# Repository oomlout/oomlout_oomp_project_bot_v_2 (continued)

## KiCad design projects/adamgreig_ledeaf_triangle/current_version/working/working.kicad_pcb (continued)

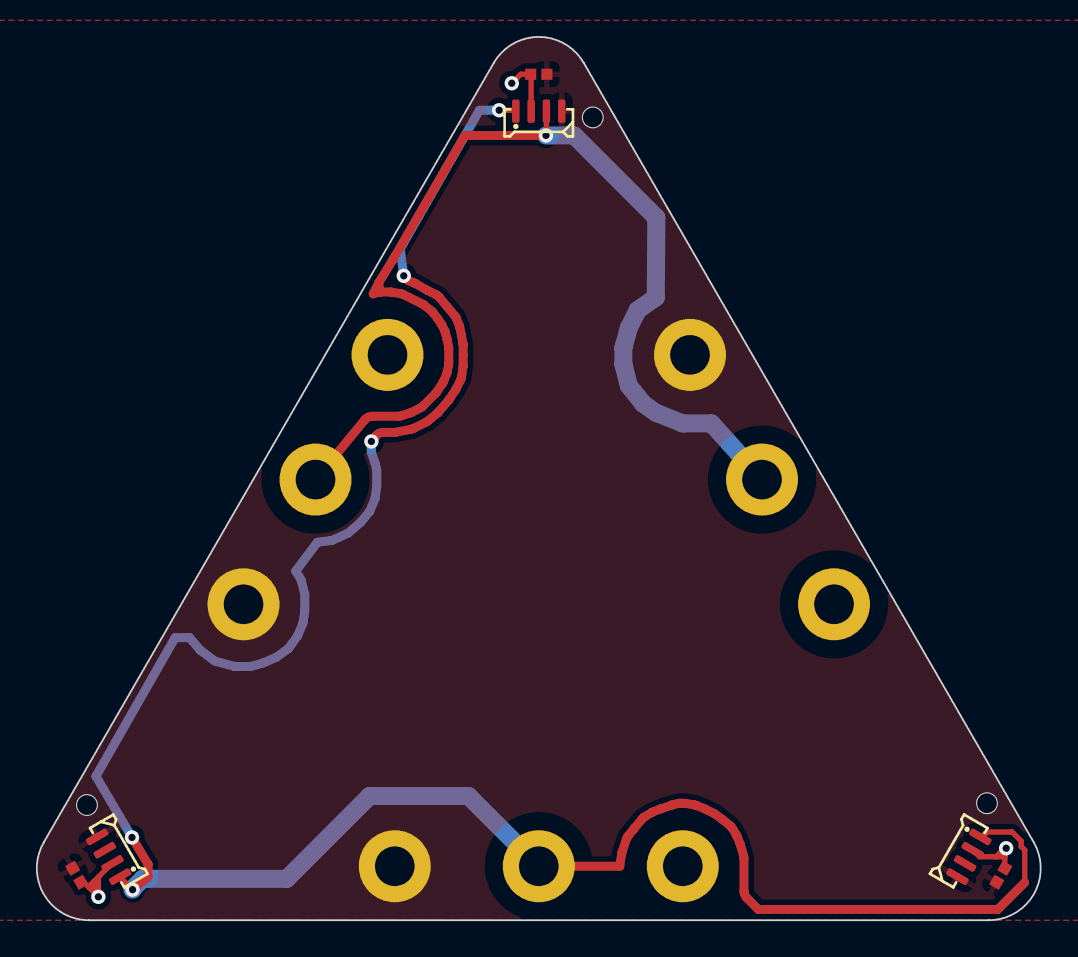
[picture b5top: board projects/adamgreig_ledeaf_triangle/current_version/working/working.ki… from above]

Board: 2 copper layers, 55.8 x 49.1 mm, 18 parts (0 on the bottom side), 4 nets.

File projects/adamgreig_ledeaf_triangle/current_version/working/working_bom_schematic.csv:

"Source:","C:\gh\oomlout_oomp_project_bot_v_2\projects\adamgreig_ledeaf_triangle\current_version\working\working.kicad_sch"
"Date:","17/09/2023 22:56:52"
"Tool:","Eeschema 7.0.6"
"Generator:","C:/Program Files/KiCad/7.0/bin/scripting/plugins/bom_csv_grouped_by_value_with_fp.py"
"Component Count:","18"
"Ref","Qnty","Value","Cmp name","Footprint","Description","Vendor","DNP"
"C1, C2, C3","3","100n","C","agg:0402","","",""
"J1, J4, J7","3","GND","CONN_01x01","agg:M2_PTH","","",""
"J2","1","DIN","CONN_01x01","agg:M2_PTH","","",""
"J3, J6, J9","3","5V","CONN_01x01","agg:M2_PTH","","",""
"J5, J8","2","DOUT","CONN_01x01","agg:M2_PTH","","",""
"LED1, LED2, LED3","3","WS2812B-4020","WS2812B-4020","agg:WS2812B-4020","Side-view RGB LED","",""
"X1, X2, X3","3","TOOLING","PART","agg:M2.5_HOLE","Generic placeholder part","",""

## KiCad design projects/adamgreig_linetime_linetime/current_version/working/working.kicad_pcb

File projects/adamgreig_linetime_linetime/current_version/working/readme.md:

# linetime
 
## summary 
* id: adamgreig_linetime_linetime
* user: adamgreig
* name: linetime
* board: linetime
* repo: https://github.com/adamgreig/linetime
* src_file_repo_kicad_pcb: hardware/linetime.kicad_pcb
* src_file_repo_kicad_pcb_link: https://github.com/adamgreig/linetime/tree/master/hardware/linetime.kicad_pcb

* src_file_repo_sch: hardware/linetime.sch
* src_file_repo_sch_link: https://github.com/adamgreig/linetime/tree/master/hardware/linetime.sch
* full details link: https://github.com/oomlout/oomlout_oomp_project_bot_v_2/tree/main/projects/adamgreig_linetime_linetime/current_version/working  

## schematic  
  
[schematic (pdf)](working_schematic.pdf) 

## pcb  

[board (pdf)](working.pdf)  

## working_bom
| Id | Designator | Footprint | Quantity | Designation | Supplier and ref |  | None | 
| --- | --- | --- | --- | --- | --- | --- | --- | 
| 1 | Y401 | XTAL-50x32 | 1 | XTAL |  |  | [''] | 
| 2 | IC201 | VTX-214-003-1xx | 1 | VTX-214-003-105 |  |  | [''] | 
| 3 | Y301 | TG-5006CG | 1 | 26M TCXO |  |  | [''] | 
| 4 | IC603 | SSOP-20 | 1 | AR1021 |  |  | [''] | 
| 5 | IC103 | SOT-23-6 | 1 | 25AA02E48 |  |  | [''] | 
| 6 | IC302 | SOT-23-5 | 1 | NC7SZ04 |  |  | [''] | 
| 7 | Q601 | SOT-23 | 1 | NFET |  |  | [''] | 
| 8 | R201 | SOT-23 | 1 | 1k/5k |  |  | [''] | 
| 9 | R202 | SOT-23 | 1 | 1k/1k |  |  | [''] | 
| 10 | D603,D604,D602,D601 | SOD-123 | 4 | ~ |  |  | [''] | 
| 11 | P301 | SMA-PTH | 1 | COAX |  |  | [''] | 
| 12 | IC203 | SC-70-6 | 1 | ADCMP601 |  |  | [''] | 
| 13 | IC401 | RJHSE-538X | 1 | RJHSE-5381 |  |  | [''] | 
| 14 | IC402 | QFN-24-EP-MICREL | 1 | KSZ8081RNx |  |  | [''] | 
| 15 | IC501 | QFN-16-EP-TI | 1 | BQ24232HA |  |  | [''] | 
| 16 | IC602 | MSOP-8 | 1 | SSM2305 |  |  | [''] | 
| 17 | IC301,IC202,IC102 | MSOP-8 | 3 | ADP3335 |  |  | [''] | 
| 18 | IC204 | MSOP-8 | 1 | ADA4528-2 |  |  | [''] | 
| 19 | IC304 | MSOP-10 | 1 | CS2100-CP |  |  | [''] | 
| 20 | IC303 | MAX-M8Q | 1 | MAX-M8Q |  |  | [''] | 
| 21 | IC101 | LQFP-144 | 1 | STM32F7xxZxTx |  |  | [''] | 
| 22 | P101 | FTSH-105-01-F-D-K | 1 | SWD |  |  | [''] | 
| 23 | J201 | DD21.01xx.1111 | 1 | FUSED INLET |  |  | [''] | 
| 24 | C203 | B32921 | 1 | X2 |  |  | [''] | 
| 25 | C201,C202 | B32921 | 2 | Y2 |  |  | [''] | 
| 26 | T201 | AVB0.35_2_X | 1 | AVB0.35/2/6 |  |  | [''] | 
| 27 | T401 | 749010012A | 1 | 749013011A |  |  | [''] | 
| 28 | D103,D102,D101 | 0603-LED | 3 | LED |  |  | [''] | 
| 29 | C209,C205,C121,C301,C308,C610,C611,C212 | 0603 | 8 | 10n |  |  | [''] | 
| 30 | C118,C117,C408 | 0603 | 3 | 2Âµ2 |  |  | [''] | 
| 31 | C208,C403,C119,C210,C211,C303,C305,C306,C307,C603,C602,C607,C411,C609,C109,C116,C115,C114,C113,C101,C112,C110,C405,C108,C107,C106,C404,C407,C102,C111,C105 | 0603 | 31 | 100n |  |  | [''] | 
| 32 | C207,C304 | 0603 | 2 | 1n |  |  | [''] | 
| 33 | C206,C204,C122,C120,C302,C104,C309 | 0603 | 7 | 1Âµ |  |  | [''] | 
| 34 | C409,C410 | 0603 | 2 | 30p |  |  | [''] | 
| 35 | C402,C406 | 0603 | 2 | 22Âµ |  |  | [''] | 
| 36 | R108,R104,R106,R107,R105 | 0603 | 5 | 47k |  |  | [''] | 
| 37 | C502,C503,C501,C103 | 0603 | 4 | 4Âµ7 |  |  | [''] | 
| 38 | C606,C604 | 0603 | 2 | 47n |  |  | [''] | 
| 39 | C605,C601,C608 | 0603 | 3 | 10Âµ |  |  | [''] | 
| 40 | R601,R602,R409,R103,R101,R102,R401 | 0603 | 7 | 1k |  |  | [''] | 
| 41 | R604,R603 | 0603 | 2 | 110k |  |  | [''] | 
| 42 | R407,R408,R405,R404,R205,R303,R411,R413,R412 | 0603 | 9 | 33 |  |  | [''] | 
| 43 | R505,R504 | 0603 | 2 | 100k |  |  | [''] | 
| 44 | R503,R410,R606,R2,R1 | 0603 | 5 | 10k |  |  | [''] | 
| 45 | R502,R204,R203 | 0603 | 3 | DNS |  |  | [''] | 
| 46 | R501 | 0603 | 1 | 4k32 |  |  | [''] | 
| 47 | L201,L401 | 0603 | 2 | FB |  |  | [''] | 
| 48 | L301 | 0603 | 1 | 27n |  |  | [''] | 
| 49 | R406 | 0603 | 1 | 6k49 |  |  | [''] | 
| 50 | R403,R402 | 0603 | 2 | 75 |  |  | [''] | 
| 51 | R302 | 0603 | 1 | 10 |  |  | [''] | 
| 52 | R605 | 0603 | 1 | 20k |  |  | [''] | 
| 53 | R301 | 0603 | 1 | 1M |  |  | [''] | 
| 54 | D301,D605,D606,D607,D608 | 0402 | 5 | ESD_DIODE |  |  | [''] | 
| 55 | C401 | 1206 | 1 | 1n 2kV |  |  | [''] | 
| 56 | LS601 | KSSG1708 | 1 | KSSG1708 |  |  | [''] | 
| 57 | R206 | 0603 | 1 | 100 |  |  | [''] | 
| 58 | U101 | MICROSD_MOLEX_503398-1892 | 1 | MICROSD |  |  | [''] | 
| 59 | IC601 | ER-CON50HT-1 | 1 | ER-TFT023-1 |  |  | [''] | 
| 60 | J501 | S02B-PASK-2 | 1 | BATT |  |  | [''] | 

## bom_schematic
| Ref | Qnty | Value | Cmp name | Footprint | Description | Vendor | DNP | 
| --- | --- | --- | --- | --- | --- | --- | --- | 
| C101, C102, C105, C106, C107, C108, C109, C110, C111, C112, C113, C114, C115, C116, C119 | 15 | 100n | C | agg:0603 |  |  |  | 
| C103 | 1 | 4Âµ7 | C | agg:0603 |  |  |  | 
| C104, C120, C122 | 3 | 1Âµ | C | agg:0603 |  |  |  | 
| C117, C118 | 2 | 2Âµ2 | C | agg:0603 |  |  |  | 
| C121 | 1 | 10n | C | agg:0603 |  |  |  | 
| D101, D102, D103 | 3 | LED | LED | agg:0603-LED |  |  |  | 
| IC101 | 1 | STM32F7xxZxTx | STM32F7xxZxTx | agg:LQFP-144 |  |  |  | 
| IC102 | 1 | ADP3335 | ADP3335 | agg:MSOP-8 |  |  |  | 
| IC103 | 1 | 25AA02E48 | 25AA02E48 | agg:SOT-23-6 |  |  |  | 
| P101 | 1 | SWD | SWD | agg:FTSH-105-01-F-D-K |  |  |  | 
| R101, R102, R103 | 3 | 1k | R | agg:0603 |  |  |  | 
| R104, R105, R106, R107, R108 | 5 | 47k | R | agg:0603 |  |  |  | 
| U101 | 1 | MICROSD | MICROSD | agg:MICROSD_MOLEX_503398-1892 |  |  |  |

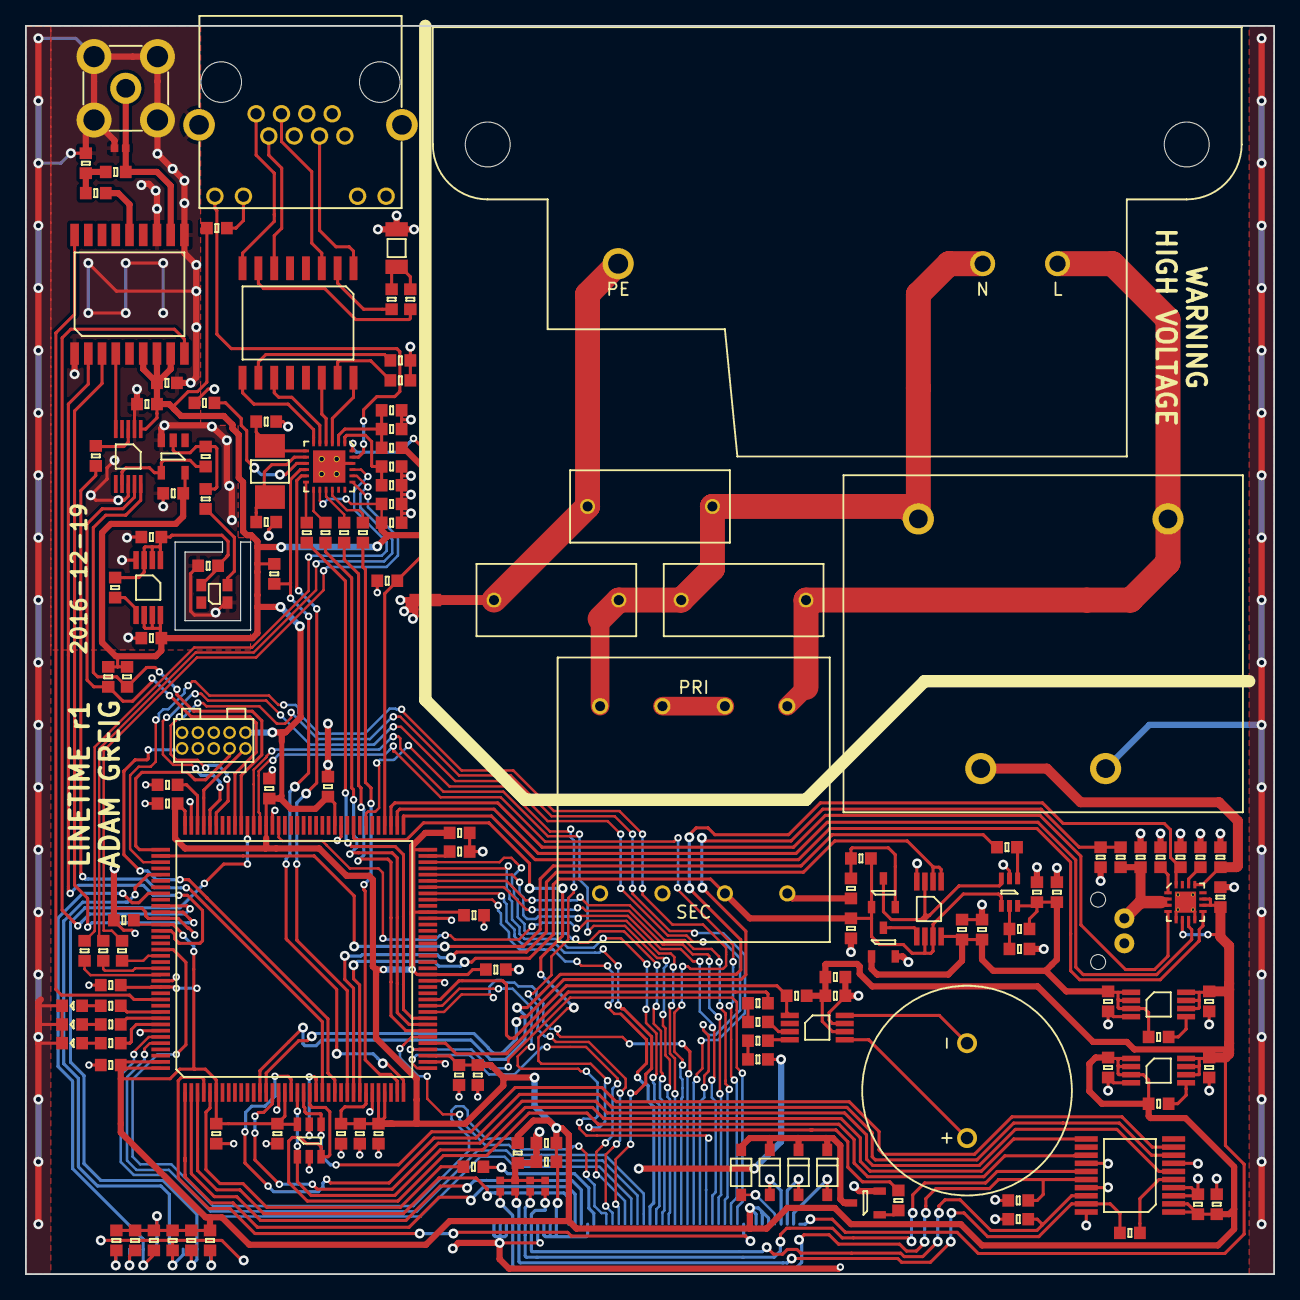
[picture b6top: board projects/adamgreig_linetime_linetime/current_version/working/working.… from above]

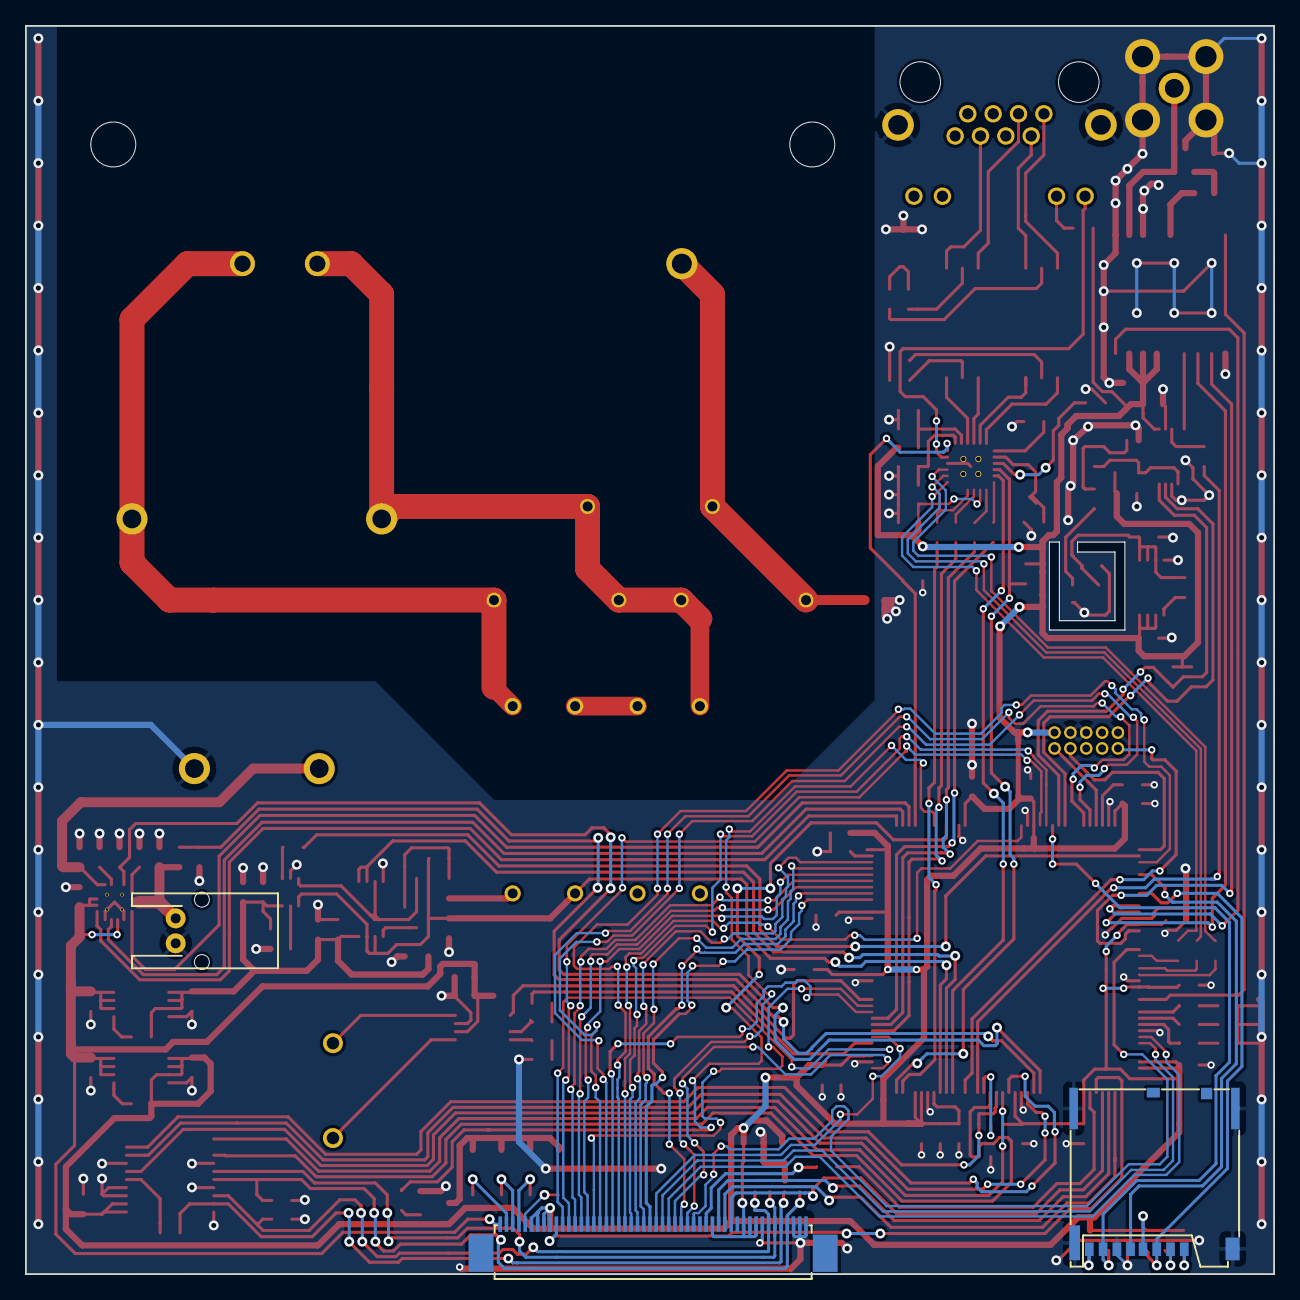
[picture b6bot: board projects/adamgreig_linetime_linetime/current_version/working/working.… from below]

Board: 2 copper layers, 100.0 x 100.0 mm, 154 parts (3 on the bottom side), 153 nets.

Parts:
C101, C102, C105, C106, C107, C108, C109, C110, C111, C112, C113, C114, C115, C116, C119, C208, C210, C211, C303, C305, C306, C307, C403, C404, C405, C407, C411, C602, C603, C607, C609: 100n; 0603
C103, C501, C502, C503: 4µ7; 0603
C104, C120, C122, C204, C206, C302, C309: 1µ; 0603
C117, C118, C408: 2µ2; 0603
C121, C205, C209, C212, C301, C308, C610, C611: 10n; 0603
C201, C202: Y2; B32921
C203: X2; B32921
C207, C304: 1n; 0603
C401: 1n 2kV; 1206
C402, C406: 22µ; 0603
C409, C410: 30p; 0603
C601, C605, C608: 10µ; 0603
C604, C606: 47n; 0603
D101, D102, D103: LED; 0603-LED
D301, D605, D606, D607, D608: ESD_DIODE; 0402
D601, D602, D603, D604: SOD-123
IC101: STM32F7xxZxTx; LQFP-144
IC102, IC202, IC301: ADP3335; MSOP-8
IC103: 25AA02E48; SOT-23-6
IC201: VTX-214-003-105; VTX-214-003-1xx
IC203: ADCMP601; SC-70-6
IC204: ADA4528-2; MSOP-8
IC302: NC7SZ04; SOT-23-5
IC303: MAX-M8Q
IC304: CS2100-CP; MSOP-10
IC401: RJHSE-5381; RJHSE-538X
IC402: KSZ8081RNx; QFN-24-EP-MICREL
IC501: BQ24232HA; QFN-16-EP-TI
IC601: ER-TFT023-1; ER-CON50HT-1
IC602: SSM2305; MSOP-8
IC603: AR1021; SSOP-20
J201: FUSED INLET; DD21.01xx.1111
J501: BATT; S02B-PASK-2
L201, L401: FB; 0603
L301: 27n; 0603
LS601: KSSG1708
P101: SWD; FTSH-105-01-F-D-K
P301: COAX; SMA-PTH
Q601: NFET; SOT-23
R1, R2, R410, R503, R606: 10k; 0603
R101, R102, R103, R401, R409, R601, R602: 1k; 0603
R104, R105, R106, R107, R108: 47k; 0603
R201: 1k/5k; SOT-23
R202: 1k/1k; SOT-23
R203, R204, R502: DNS; 0603
R205, R303, R404, R405, R407, R408, R411, R412, R413: 33; 0603
R206: 100; 0603
R301: 1M; 0603
R302: 10; 0603
R402, R403: 75; 0603
R406: 6k49; 0603
R501: 4k32; 0603
R504, R505: 100k; 0603
R603, R604: 110k; 0603
R605: 20k; 0603
T201: AVB0.35/2/6; AVB0.35_2_X
T401: 749013011A; 749010012A
U101: MICROSD; MICROSD_MOLEX_503398-1892
Y301: 26M TCXO; TG-5006CG
Y401: XTAL; XTAL-50x32

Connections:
3v3: C101.1, C102.1, C103.1, C104.1, C105.1, C106.1, C107.1, C108.1, C109.1, C110.1, C111.1, C112.1, C113.1, C114.1, C115.1, C116.1, C119.1, C121.2, C122.1, C305.1, C306.1, C307.1, C309.1, C406.2, C407.2, C601.1, C602.1, C603.1, C608.1, C609.1, IC101.6, IC101.17, IC101.30, IC101.32, IC101.33, IC101.39, IC101.52, IC101.62, IC101.72, IC101.84, IC101.95, IC101.108, IC101.121, IC101.131, IC101.143, IC101.144, IC102.1, IC102.2, IC102.3, IC103.6, IC301.6, IC301.7, IC301.8, IC302.5, IC303.6, IC303.7, IC303.8, IC304.1, IC402.14, IC601.6, IC601.7, IC601.8, IC601.9, IC601.35, IC601.40, IC601.41, IC601.42, IC603.1, IC603.2, L401.2, P101.1, R1.1, R2.1, R104.1, R105.1, R106.1, R107.1, R108.1, R401.2, R409.2, U101.4
/B2: IC101.125, IC601.32
/B3: IC101.79, IC601.31
/B4: IC101.65, IC601.30
/B5: IC101.37, IC601.29
/B6: IC101.139, IC601.28
/B7: IC101.140, IC601.27
/BACKLIGHT: IC101.81, R601.2
/CRS_DV: IC101.43, R405.2
/CS2100_CLK: IC101.23, R303.2
/CS2100_SDA: IC101.99, IC304.10, R1.2
/DE: IC101.66, IC601.14
/DOTCLK: IC101.67, IC601.13
/G2: IC101.42, IC601.26
/G3: IC101.64, IC601.25
/G4: IC101.69, IC601.24
/G5: IC101.70, IC601.23
/G6: IC101.97, IC601.22
/G7: IC101.93, IC601.21
/GPS_PPS: IC101.133, IC303.18
/GPS_RXD: IC101.119, IC303.3
/GPS_TXD: IC101.122, IC303.2
/GPS_~RESET: IC101.118, IC303.9
/HSYNC: IC101.96, IC601.12
/I_CHG: IC101.13, IC501.16, R501.2
/LED1: IC101.135, R101.1
/LED2: IC101.136, R102.1
/LED3: IC101.137, R103.1
/MAINS_BIAS: C207.2, C208.1, IC101.29, IC203.4, IC204.6, IC204.7, R201.1, T201.7
/MAINS_WAVE: IC101.28, IC204.1, IC204.2
/MAINS_ZC: IC101.110, R205.2
/MDC: IC101.27, IC402.11
/MDIO: IC101.36, IC402.10, R409.1
/PHY_~RST: IC101.76, IC402.24, R410.1
/R2: IC101.111, IC601.20
/R3: IC101.46, IC601.19
/R4: IC101.103, IC601.18
/R5: IC101.104, IC601.17
/R6: IC101.47, IC601.16
/R7: IC101.68, IC601.15
/REF_CLK: IC101.35, R408.2
/ROM_SCK: IC101.19, IC103.1, IC603.11
/ROM_SI: IC101.21, IC103.3, IC603.13
/ROM_SO: IC101.20, IC103.4, IC603.9
/ROM_~CS: IC101.22, IC103.5
/RXD0: IC101.44, R407.2
/RXD1: IC101.45, R404.2
/SD2100_SCL: IC101.100, IC304.9, R2.2
/SOUNDER: C606.1, IC101.41
/SOUNDER_~SD: IC101.48, IC602.1, R606.2
/SWCLK: IC101.109, P101.4
/SWDIO: IC101.105, P101.2
/TFT_DCX: IC101.2, IC601.36
/TFT_RESET: IC101.4, IC601.10
/TFT_SCL: IC101.1, IC601.37
/TFT_SDA: IC101.5, R602.2
/TFT_~CS: IC101.3, IC601.38
/TOUCH_INT: IC101.15, IC603.6
/TOUCH_~CS: IC101.18, IC603.8
/TXD0: IC101.128, R413.2
/TXD1: IC101.129, R412.2
/TXEN: IC101.126, R411.2
/VSYNC: IC101.40, IC601.11
/V_BATT_MON: IC101.14, R504.2, R505.1
/linetime_battery/DC_IN: C501.1, IC201.3, IC501.13
/linetime_ethernet/CT1: R402.1, T401.2
/linetime_ethernet/CT2: R403.1, T401.7
/linetime_ethernet/LINK_LED: IC401.9, IC402.23
/linetime_mains/EARTH: C201.2, C202.2, J201.3, L201.2
/linetime_mains/LIVE: C203.1, IC201.1, J201.1, T201.1
/linetime_mains/NEUTRAL: C201.1, C202.1, C203.2, IC201.2, J201.2, T201.4
/linetime_ui/X+: C610.1, D608.1, IC601.44, IC603.18
/linetime_ui/X-: D606.1, IC601.46, IC603.19, R605.1
/linetime_ui/Y+: D607.1, IC601.45, IC603.15
/linetime_ui/Y-: C611.1, D605.1, IC601.47, IC603.16
/nRST: IC101.25, P101.10
/uSD_CLK: IC101.113, U101.5
/uSD_CMD: IC101.116, R106.2, U101.3
/uSD_DAT0: IC101.98, R104.2, U101.7
/~CE: IC101.75, IC501.4
/~CHG: IC101.73, IC501.9
/~PGOOD: IC101.74, IC501.7
AVCC: C205.2, C206.1, C209.1, C210.1, C211.1, C212.1, IC202.1, IC202.2, IC202.3, IC203.6, IC204.8, R202.1, R203.1
GND: C101.2, C102.2, C103.2, C104.2, C105.2, C106.2, C107.2, C108.2, C109.2, C110.2, C111.2, C112.2, C113.2, C114.2, C115.2, C116.2, C117.2, C118.2, C119.2, C120.2, C122.2, C204.2, C206.2, C208.2, C209.2, C210.2, C211.2, C212.2, C302.2, C303.2, C305.2, C306.2, C307.2, C308.2, C309.2, C401.2, C402.1, C403.2, C404.2, C405.1, C406.1, C407.1, C408.1, C409.2, C410.2, C411.1, C501.2, C502.2, C503.2, C601.2, C602.2, C603.2, C604.1, C605.2, C607.2, C608.2, C609.2, C610.2, C611.2, D101.1, D102.1, D103.1, D301.1, D605.2, D606.2, D607.2, D608.2, IC101.16, IC101.31, IC101.38, IC101.51, IC101.61, IC101.83, IC101.94, IC101.107, IC101.120, IC101.130, IC101.138, IC102.4, IC103.2, IC201.4, IC202.4, IC203.2, IC204.4, IC301.4, IC302.3, IC303.1, IC303.10, IC303.12, IC304.2, IC304.8, IC401.S, IC402.22, IC402.EP, IC501.5, IC501.8, IC501.EP, IC601.43, IC601.48, IC601.49, IC601.50, IC602.7, IC603.3, IC603.4, IC603.7, IC603.14, IC603.17, IC603.20, J501.1, L201.1, P101.3, P101.5, P101.9, P301.2, Q601.2, R202.2, R204.2, R406.2, R410.2, R501.1, R502.1, R503.1, R505.2, U101.6, U101.9, Y301.2
unnamed: C117.1, IC101.71
unnamed: C118.1, IC101.106
unnamed: C121.1, IC102.5
unnamed: C205.1, IC202.5
unnamed: C207.1, R201.2, R206.1
unnamed: C301.1, IC301.5
unnamed: C301.2, C302.1, C303.1, IC301.1, IC301.2, IC301.3, Y301.4
unnamed: C304.1, Y301.3
unnamed: C304.2, IC302.2, R301.1
unnamed: C308.1, L301.1, R302.2
unnamed: C401.1, R402.2, R403.2
unnamed: C402.2, C405.2, IC402.2, L401.1
unnamed: C403.1, T401.15
unnamed: C404.1, T401.10
unnamed: C408.2, C411.2, IC402.1
unnamed: C409.1, IC402.7, Y401.1
unnamed: C410.1, IC402.8, Y401.2
unnamed: C503.1, IC501.2, IC501.3, J501.2, R504.1
unnamed: C604.2, R603.1
unnamed: C606.2, R604.1
unnamed: D101.2, R101.2
unnamed: D102.2, R102.2
unnamed: D103.2, R103.2
unnamed: D301.2, IC303.11, L301.2, P301.1
unnamed: D601.1, D602.1, D603.1, D604.1, Q601.3
unnamed: D601.2, IC601.3
unnamed: D602.2, IC601.5
unnamed: D603.2, IC601.2
unnamed: D604.2, IC601.4
unnamed: IC203.1, R205.1
unnamed: IC203.3, IC204.3, R201.3
unnamed: IC203.5, R203.2, R204.1
unnamed: IC204.5, R202.3
unnamed: IC302.4, IC304.7, R301.2
unnamed: IC303.4, IC304.5
unnamed: IC303.14, R302.1
unnamed: IC304.3, R303.1
unnamed: IC401.1, T401.8
unnamed: IC401.2, T401.6
unnamed: IC401.3, T401.3
unnamed: IC401.6, T401.1
unnamed: IC401.10, R401.1
unnamed: IC402.3, T401.16
unnamed: IC402.4, T401.14
unnamed: IC402.5, T401.11
unnamed: IC402.6, T401.9
unnamed: IC402.9, R406.1
unnamed: IC402.12, R404.1
unnamed: IC402.13, R407.1
unnamed: IC402.15, R405.1
unnamed: IC402.16, R408.1
unnamed: IC402.19, R411.1
unnamed: IC402.20, R413.1
unnamed: IC402.21, R412.1
unnamed: IC501.1, R503.2
unnamed: IC501.14, R502.2
unnamed: IC601.34, R602.1
unnamed: IC602.3, R604.2
unnamed: IC602.4, R603.2
unnamed: IC602.5, LS601.1
unnamed: IC602.8, LS601.2
unnamed: IC603.5, R605.2
unnamed: Q601.1, R601.1
unnamed: R105.2, U101.1
unnamed: R107.2, U101.8
unnamed: R108.2, U101.2
unnamed: R206.2, T201.8
unnamed: T201.2, T201.3
VCC: C120.1, C204.1, C502.1, C605.1, C607.1, IC102.6, IC102.7, IC102.8, IC202.6, IC202.7, IC202.8, IC501.6, IC501.10, IC501.11, IC601.1, IC602.6, R606.1

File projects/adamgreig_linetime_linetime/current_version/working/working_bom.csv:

"Id";"Designator";"Footprint";"Quantity";"Designation";"Supplier and ref";
1;"Y401";"XTAL-50x32";1;"XTAL";;;
2;"IC201";"VTX-214-003-1xx";1;"VTX-214-003-105";;;
3;"Y301";"TG-5006CG";1;"26M TCXO";;;
4;"IC603";"SSOP-20";1;"AR1021";;;
5;"IC103";"SOT-23-6";1;"25AA02E48";;;
6;"IC302";"SOT-23-5";1;"NC7SZ04";;;
7;"Q601";"SOT-23";1;"NFET";;;
8;"R201";"SOT-23";1;"1k/5k";;;
9;"R202";"SOT-23";1;"1k/1k";;;
10;"D603,D604,D602,D601";"SOD-123";4;"~";;;
11;"P301";"SMA-PTH";1;"COAX";;;
12;"IC203";"SC-70-6";1;"ADCMP601";;;
13;"IC401";"RJHSE-538X";1;"RJHSE-5381";;;
14;"IC402";"QFN-24-EP-MICREL";1;"KSZ8081RNx";;;
15;"IC501";"QFN-16-EP-TI";1;"BQ24232HA";;;
16;"IC602";"MSOP-8";1;"SSM2305";;;
17;"IC301,IC202,IC102";"MSOP-8";3;"ADP3335";;;
18;"IC204";"MSOP-8";1;"ADA4528-2";;;
19;"IC304";"MSOP-10";1;"CS2100-CP";;;
20;"IC303";"MAX-M8Q";1;"MAX-M8Q";;;
21;"IC101";"LQFP-144";1;"STM32F7xxZxTx";;;
22;"P101";"FTSH-105-01-F-D-K";1;"SWD";;;
23;"J201";"DD21.01xx.1111";1;"FUSED INLET";;;
24;"C203";"B32921";1;"X2";;;
25;"C201,C202";"B32921";2;"Y2";;;
26;"T201";"AVB0.35_2_X";1;"AVB0.35/2/6";;;
27;"T401";"749010012A";1;"749013011A";;;
28;"D103,D102,D101";"0603-LED";3;"LED";;;
29;"C209,C205,C121,C301,C308,C610,C611,C212";"0603";8;"10n";;;
30;"C118,C117,C408";"0603";3;"2µ2";;;
31;"C208,C403,C119,C210,C211,C303,C305,C306,C307,C603,C602,C607,C411,C609,C109,C116,C115,C114,C113,C101,C112,C110,C405,C108,C107,C106,C404,C407,C102,C111,C105";"0603";31;"100n";;;
32;"C207,C304";"0603";2;"1n";;;
33;"C206,C204,C122,C120,C302,C104,C309";"0603";7;"1µ";;;
34;"C409,C410";"0603";2;"30p";;;
35;"C402,C406";"0603";2;"22µ";;;
36;"R108,R104,R106,R107,R105";"0603";5;"47k";;;
37;"C502,C503,C501,C103";"0603";4;"4µ7";;;
38;"C606,C604";"0603";2;"47n";;;
39;"C605,C601,C608";"0603";3;"10µ";;;
40;"R601,R602,R409,R103,R101,R102,R401";"0603";7;"1k";;;
41;"R604,R603";"0603";2;"110k";;;
42;"R407,R408,R405,R404,R205,R303,R411,R413,R412";"0603";9;"33";;;
43;"R505,R504";"0603";2;"100k";;;
44;"R503,R410,R606,R2,R1";"0603";5;"10k";;;
45;"R502,R204,R203";"0603";3;"DNS";;;
46;"R501";"0603";1;"4k32";;;
47;"L201,L401";"0603";2;"FB";;;
48;"L301";"0603";1;"27n";;;
49;"R406";"0603";1;"6k49";;;
50;"R403,R402";"0603";2;"75";;;
51;"R302";"0603";1;"10";;;
52;"R605";"0603";1;"20k";;;
53;"R301";"0603";1;"1M";;;
54;"D301,D605,D606,D607,D608";"0402";5;"ESD_DIODE";;;
55;"C401";"1206";1;"1n 2kV";;;
56;"LS601";"KSSG1708";1;"KSSG1708";;;
57;"R206";"0603";1;"100";;;
58;"U101";"MICROSD_MOLEX_503398-1892";1;"MICROSD";;;
59;"IC601";"ER-CON50HT-1";1;"ER-TFT023-1";;;
60;"J501";"S02B-PASK-2";1;"BATT";;;

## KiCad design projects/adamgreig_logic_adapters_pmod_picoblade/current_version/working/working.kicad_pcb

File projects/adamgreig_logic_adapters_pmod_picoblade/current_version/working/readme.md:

# logic_adapters
 
## summary 
* id: adamgreig_logic_adapters_pmod_picoblade
* user: adamgreig
* name: logic_adapters
* board: pmod_picoblade
* repo: https://github.com/adamgreig/logic_adapters
* src_file_repo_kicad_pcb: pmod_picoblade/pmod_picoblade.kicad_pcb
* src_file_repo_kicad_pcb_link: https://github.com/adamgreig/logic_adapters/tree/master/pmod_picoblade/pmod_picoblade.kicad_pcb

* src_file_repo_sch: pmod_picoblade/pmod_picoblade.sch
* src_file_repo_sch_link: https://github.com/adamgreig/logic_adapters/tree/master/pmod_picoblade/pmod_picoblade.sch
* full details link: https://github.com/oomlout/oomlout_oomp_project_bot_v_2/tree/main/projects/adamgreig_logic_adapters_pmod_picoblade/current_version/working  

## schematic  
  
[schematic (pdf)](working_schematic.pdf) 

## pcb  

[board (pdf)](working.pdf)  

## working_bom
| Id | Designator | Footprint | Quantity | Designation | Supplier and ref |  | None | 
| --- | --- | --- | --- | --- | --- | --- | --- | 
| 1 | J1,J2 | DIL-254P-08 | 2 | SALEAE_0-3 |  |  | [''] | 
| 2 | J4 | DIL-254P-12 | 1 | PMOD |  |  | [''] | 
| 3 | J5,J6 | DIL-254P-08 | 2 | SALEAE_4-7 |  |  | [''] | 
| 4 | J3 | MOLEX-PICOBLADE-53398-0771 | 1 | SPI |  |  | [''] | 
| 5 | J7 | MOLEX-PICOBLADE-53398-0471 | 1 | UART |  |  | [''] | 

## bom_schematic
| Ref | Qnty | Value | Cmp name | Footprint | Description | Vendor | DNP | 
| --- | --- | --- | --- | --- | --- | --- | --- | 
| J1, J2 | 2 | SALEAE_0-3 | CONN_02x04-agg | agg:DIL-254P-08 |  |  |  | 
| J3 | 1 | SPI | CONN_01x07-agg | agg:MOLEX-PICOBLADE-53398-0771 |  |  |  | 
| J4 | 1 | PMOD | CONN_02x06-agg | agg:DIL-254P-12 |  |  |  | 
| J5, J6 | 2 | SALEAE_4-7 | CONN_02x04-agg | agg:DIL-254P-08 |  |  |  | 
| J7 | 1 | UART | CONN_01x04-agg | agg:MOLEX-PICOBLADE-53398-0471 |  |  |  |

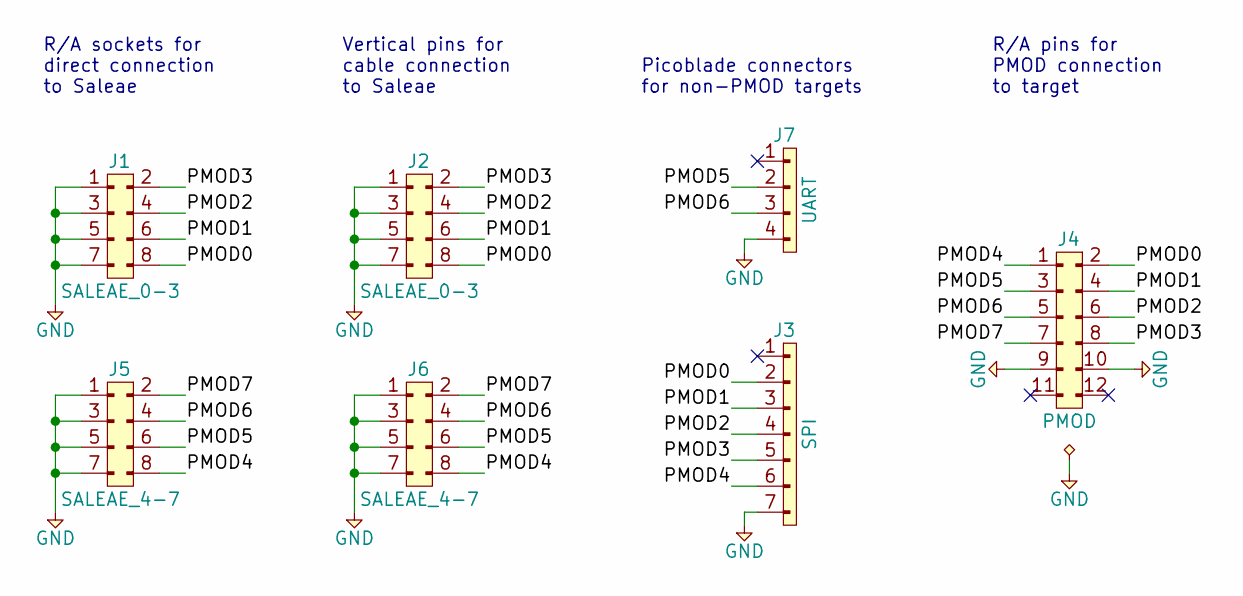
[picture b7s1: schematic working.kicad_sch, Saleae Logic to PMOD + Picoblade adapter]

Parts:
J1: SALEAE_0-3; DIL-254P-08; Farnell 1668343
J2: SALEAE_0-3; DIL-254P-08; Farnell 2856692
J3: SPI; MOLEX-PICOBLADE-53398-0771; Farnell 9786368
J4: PMOD; DIL-254P-12; Farnell 2032721
J5: SALEAE_4-7; DIL-254P-08; Farnell 1668343
J6: SALEAE_4-7; DIL-254P-08; Farnell 2856692
J7: UART; MOLEX-PICOBLADE-53398-0471; Farnell 1125367

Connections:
/PMOD0: J1.8, J2.8, J3.2, J4.2
/PMOD1: J1.6, J2.6, J3.3, J4.4
/PMOD2: J1.4, J2.4, J3.4, J4.6
/PMOD3: J1.2, J2.2, J3.5, J4.8
/PMOD4: J3.6, J4.1, J5.8, J6.8
/PMOD5: J4.3, J5.6, J6.6, J7.2
/PMOD6: J4.5, J5.4, J6.4, J7.3
/PMOD7: J4.7, J5.2, J6.2
GND: J1.1, J1.3, J1.5, J1.7, J2.1, J2.3, J2.5, J2.7, J3.7, J4.9, J4.10, J5.1, J5.3, J5.5, J5.7, J6.1, J6.3, J6.5, J6.7, J7.4

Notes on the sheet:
Vertical pins for cable connection to Saleae
R/A pins for PMOD connection to target
Picoblade connectors for non-PMOD targets
R/A sockets for direct connection to Saleae

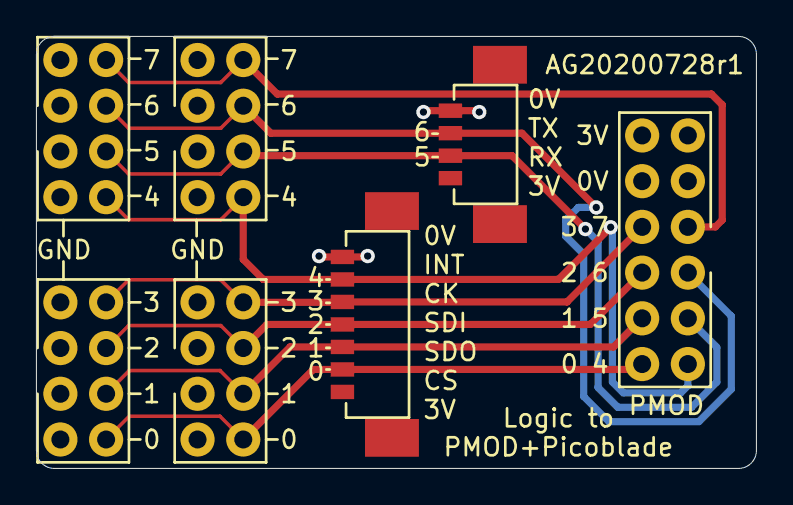
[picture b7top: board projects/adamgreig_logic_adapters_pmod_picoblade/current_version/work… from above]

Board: 2 copper layers, 40.0 x 24.0 mm, 7 parts (0 on the bottom side), 9 nets.
